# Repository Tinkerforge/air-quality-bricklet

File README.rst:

Air Quality Bricklet
====================

This repository contains the firmware source code and the hardware design
files. The documentation generator configs can be found at
https://github.com/Tinkerforge/generators

Repository Content
------------------

software/:
 * examples/: Examples for all supported languages
 * build/: Compiled files
 * src/: Source code of firmware
 * Makefile: Makefile to build project

hardware/:
 * Contains KiCad project files and additionally schematics as PDF

datasheets/:
 * Contains datasheets for sensors and complex ICs that are used

Hardware
--------

The hardware is designed with the open source EDA Suite KiCad
(http://www.kicad.org). Before you are able to open the files,
you have to install the Tinkerforge kicad-libraries
(https://github.com/Tinkerforge/kicad-libraries). You can either clone
them directly in hardware/ or clone them in a separate folder and
symlink them into hardware/
(ln -s kicad_path/kicad-libraries project_path/hardware). After that you
can open the .pro file in hardware/ with KiCad and from there view and
modify the schematics and the PCB layout.

Software
--------

If you want to do your own Brick/Bricklet firmware development we highly
recommend that you use our build environment setup script and read the
tutorial (https://www.tinkerforge.com/en/doc/Tutorials/Tutorial_Build_Environment/Tutorial.html).

To compile the C code we recommend you to install the newest GNU Arm Embedded
Toolchain (https://launchpad.net/gcc-arm-embedded/+download).
You also need to install bricklib2 (https://github.com/Tinkerforge/bricklib2).

You can either clone it directly in software/src/ or clone it in a
separate folder and symlink it into software/src/
(ln -s bricklib_path/bricklib2 project_path/software/src/). Finally make sure to
have CMake installed (http://www.cmake.org/cmake/resources/software.html).

After that you can build the firmware by invoking make in software/.
The firmware (.zbin) can then be found in software/build/ and uploaded
with brickv (click button "Flashing" on start screen).

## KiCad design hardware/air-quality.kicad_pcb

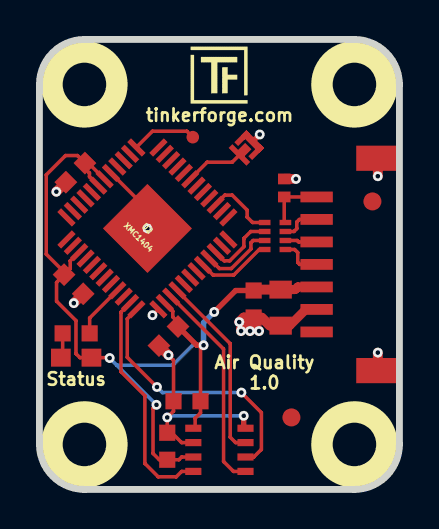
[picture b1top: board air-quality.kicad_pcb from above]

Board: 2 copper layers, 20.0 x 25.0 mm, 23 parts (1 on the bottom side), 18 nets.

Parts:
C1, C2, C3, C104, C105: 100nF; C0603F
C101: 10uF; C0805
C102: 220pF; C0402F
C103: 1uF; C0603F
D101: blue; D0603E
Fiducial_Mark: VAL**; Fiducial_Mark
Fiducial_Mark#2: VAL**; Fiducial_Mark
P101: CON-SENSOR2
P102: DEBUG; DEBUG_PAD
P103: BOOT; SolderJumper
R101: 1k; R0603F
RP101: 82; 4X0402
U1: BME680
U2: XMC1404; QFN48-EP2
U103, U104, U105, U106: DRILL; DRILL_NP
VAL: CE_5mm

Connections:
GND: C1.2, C2.2, C3.2, C101.1, C102.1, C103.1, C104.2, C105.2, P101.2, P101.EP, P103.1, U1.1, U1.7, U2.17, U2.37, U2.EP
M-CLK: U1.4, U2.39
M-CS: U1.2, U2.40
M-MISO: U1.5, U2.35
M-MOSI: U1.3, U2.36
unnamed: C102.2, P101.7, RP101.4
unnamed: D101.2, R101.2
unnamed: P101.4, RP101.1
unnamed: P101.5, RP101.2
unnamed: P101.6, RP101.3
unnamed: P102.1, U2.13
unnamed: P103.2, U2.7
unnamed: R101.1, U2.33
S-CLK: RP101.7, U2.45
S-CS: RP101.8, U2.44
S-MISO: RP101.5, U2.3
S-MOSI: RP101.6, U2.46
VCC: C1.1, C2.1, C3.1, C101.2, C103.2, C104.1, C105.1, D101.1, P101.3, U1.6, U1.8, U2.18, U2.19, U2.27, U2.38

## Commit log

2017-11-13 Add datasheet
2017-11-13 Add initial schematic
2017-11-13 Add initial PCB
2017-11-14 Add routing for BME680
2018-01-04 Change CoMCU to XMC1400
2018-01-04 Change Boot, Debug und Status LED pins
2018-01-04 Change XMC1100 to XMC1400 footprint
2018-01-08 Fix version
2018-01-08 Change some new years things
2018-02-20 Add .gitignore
2018-02-20 Cleanup KiCad libraries config
    Ensure LibDir=kicad-libraries and LibName1=tinkerforge.
    Remove special library.
2018-03-20 Add BOSCH BSEC library to gitignore
2018-03-20 Add firmware
2018-03-22 Fix bugs in save state/load
2018-03-22 Increase default offset to 3.5°C
2018-03-22 use 3.9°C offset (calibrated with VA720 calibrator)
2018-04-19 rename voc bricklet to air quality bricklet
2018-04-19 Rename voc to air quality in comments
2018-06-06 fix status text, set origin
2018-06-06 Adapt to bricklet2 callback-value changes
2018-06-07 fix wrong bypass capacitor connection, remove copper plane from sensor, increase sensor footprint pad size
2018-06-11 Rename files
2018-06-18 Change capacitor footprint(s) to C0402F
2018-06-28 Fix readme
2018-07-11 Add Makefile with docker support
2018-07-11 Fix origin
2018-07-11 Update directory structure and build instructions
2018-07-11 Remove obsolete generate_makefile scripts
2018-07-17 specify processor
2018-07-30 rename datahseet
2018-07-30 Turn logging off
2018-07-31 Add 3d model (*.FCStd & .step)
2018-07-31 Add PDF schematic
2018-08-27 Add accuracy parameter to IAQ index getter and callback
2018-08-27 Add examples
2018-09-10 examples: Fix callback configuration
2018-09-14 Fix typo in example
2018-10-02 Add BOOTLOADER_FIX_POINTER_END define
2018-10-04 Add rev to changelog
2018-10-12 Change rate from 1 SPS to 0.3SPS
    This results in a decrease of self-heating from 3.9 to 0.5°C!
2018-10-12 Update changelog with new rev and date
2018-10-16 Remove in-development marker
2018-11-06 Add rust examples
2018-11-07 rust: Accept host names for ip connection, fix naming inconsistencies
2018-11-07 rust: Rename callback receivers.
2018-12-14 Add go examples.
2018-12-14 go: Fix printf parameters.
2018-12-18 go: Change import path.
2018-12-18 go: Change import path again.
2018-12-20 rust: Fix result variable names in examples.
2018-12-20 rust: Reformat examples.
2019-01-04 Fix error in packet length for get_iaq_index function
2019-01-04 Add rev for 2.0.1
2019-01-04 Fix temperature offset (use 1/100 °C instead of °C)
2019-01-04 Update changelog rev
2019-01-24 mqtt: Add examples.
2019-01-24 mqtt: Fix example header.
2019-01-24 mqtt: Remove executable bit in example permissions.
2019-01-24 go: Minor example fixes.
2019-01-24 mqtt: Minor example fixes.
2019-02-05 Add RemoveCalibration API implementation
2019-02-05 Use sleep_time as calculated
    If we are too early because of the rounding down, we can
    handle the busy state aproprietly above.
2019-02-05 Use tabs
    The voc.c somehow ended up with a mix of spaces and tabs,
    we use tabs.
2019-02-08 Add API for changing background calibration duration
2019-02-12 Update version and changelog
2019-02-12 Add rev for 2.0.3
2019-02-22 fixed libary, added sym-lib-table, changed processor to XMC1404
2019-03-07 Add another bsec test folder to gitignore
2019-03-07 Disable automatic calibration load/save for now
    This is broken in BSEC v1.4.7.1 and it is not clear when a fixed version will be released
2019-03-07 Add ref for 2.0.4
2019-03-28 mqtt: Fix whitespace.
2019-08-14 Improve outlier value handling
2019-08-22 c: Adapt to bindings changes
2019-08-27 go: Escape '%' in examples.
2019-08-28 Correct date and add ref for 2.0.5
2019-11-22 Update examples
2020-01-13 examples: Use python3 input instead of python2 raw_input.
2020-01-13 examples: mqtt: Remove trailing whitespace.
2020-08-19 Add uc examples.
2020-08-25 uc: Fix whitespace
2020-08-27 uc: Fix warnings.
2020-08-31 uc: Use fixed-with placeholders in format strings.
2020-09-02 uc: Add example driver note.
2020-10-16 uc: Fix divisor type.
2021-07-12 Update BSEC to 1.4.8.0
    - reactivate auto-calibration
    - use 1 page for calibration save/load instead of 2
    - increase work buffer and coop task stack size
2021-07-12 Add changelog entry for 2.0.6
2021-07-12 Add ref for 2.0.6
2021-10-25 Update KiCad link
    https://www.kicad.org/blog/2021/10/Avoid-links-to-former-kicad-domain/
2022-04-19 examples: uc: Rename TF_HalContext to TF_HAL.
2022-04-27 uc: Adapt to bindings changes
2022-05-10 go: Fix format string
2022-07-06 Add license files.
2023-06-21 update to new kicad version

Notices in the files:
hardware/air-quality.kicad_pcb:
Licensed under CERN OHL v.1.1
Copyright (©) 2017, L.Lauer
Copyright Tinkerforge GmbH 2017.
This documentation describes Open Hardware and is licensed under the
CERN OHL v. 1.1.
